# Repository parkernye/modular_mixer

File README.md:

# modular_mixer
Modular Synth 3-channel Mixer

A simple 3-input / 2-output mixer to route sound from the rest of the modular synth to headphones/speaker. 

Future Imporvements:
- Add silkscreen labels to help in assembly
- Source higher quality potentiometers

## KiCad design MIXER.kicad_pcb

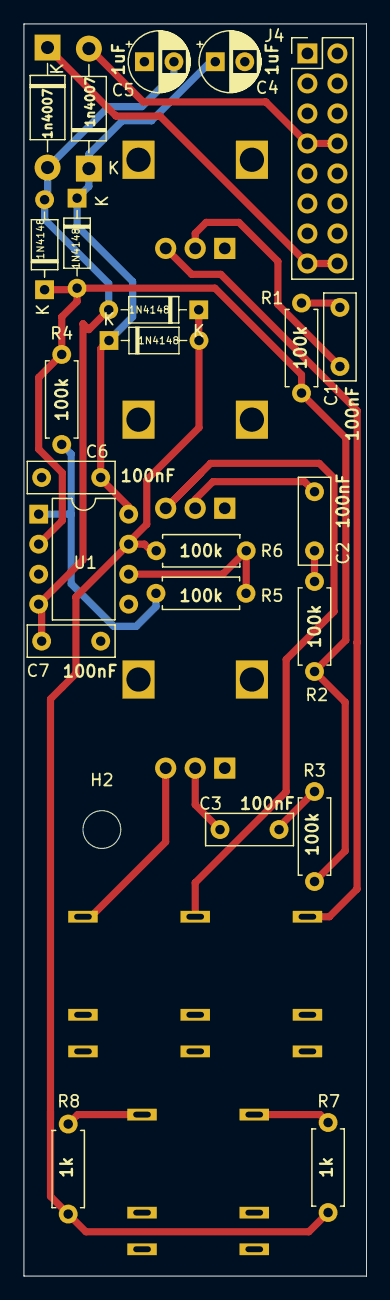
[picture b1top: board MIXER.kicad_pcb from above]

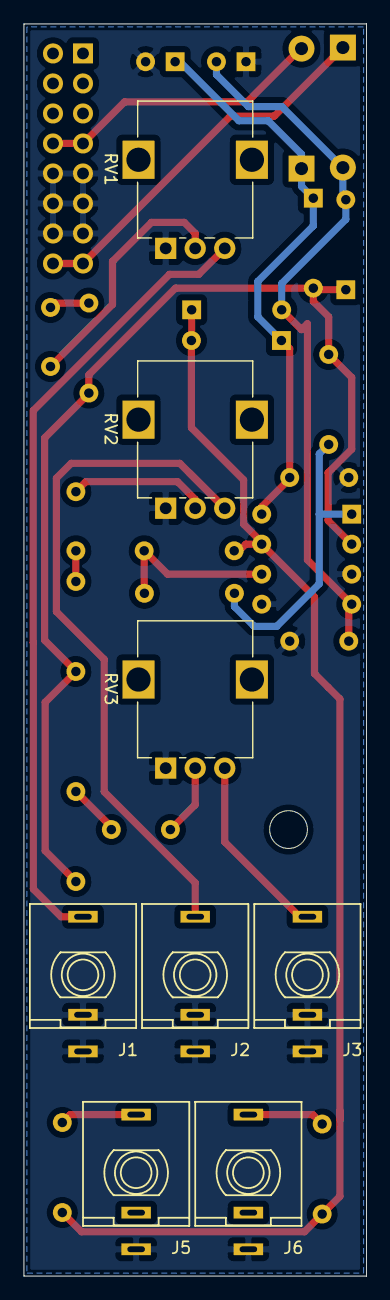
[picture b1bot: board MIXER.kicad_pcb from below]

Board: 2 copper layers, 29.0 x 106.0 mm, 33 parts (8 on the bottom side), 20 nets.

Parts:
C1, C2, C3, C6, C7: 100nF; C_Rect_L7.2mm_W2.5mm_P5.00mm_FKS2_FKP2_MKS2_MKP2
C4, C5: 1uF; CP_Radial_D5.0mm_P2.50mm
D1, D2, D5, D6: 1N4148; D_DO-35_SOD27_P7.62mm_Horizontal
D3, D4: 1N4007; D_DO-41_SOD81_P10.16mm_Horizontal
H1, H2: MountingHole; MountingHole_3.2mm_M3
J1, J2, J3, J5, J6: fuzzySI_thonkiconn; thonkiconn_fuzzySi
J4: Conn_02x08_Odd_Even; PinHeader_2x08_P2.54mm_Vertical
R1, R2, R3, R4, R5, R6: 100K; R_Axial_DIN0207_L6.3mm_D2.5mm_P7.62mm_Horizontal
R7, R8: 1K; R_Axial_DIN0207_L6.3mm_D2.5mm_P7.62mm_Horizontal
RV1, RV2, RV3: 100k; Potentiometer_Alpha_RD901F-40-00D_Single_Vertical
U1: TL072; DIP-8_W7.62mm

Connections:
+12V: C4.1, C6.1, D2.1, D3.1, D5.1, U1.8
-12V: C5.2, C7.2, D1.2, D4.2, D6.2, U1.4
GND: C4.2, C5.1, C6.2, C7.1, J1.1, J1.2, J2.1, J2.2, J3.1, J3.2, J4.9, J4.10, J4.11, J4.12, J4.13, J4.14, J5.1, J6.1, RV1.1, RV2.1, RV3.1, U1.3, U1.5
unnamed: C1.1, RV1.2
unnamed: C1.2, R1.2
unnamed: C2.1, RV2.2
unnamed: C2.2, R2.2
unnamed: C3.1, RV3.2
unnamed: C3.2, R3.2
unnamed: D1.1, D2.2, R1.1, R2.1, R3.1, R4.2, U1.2
unnamed: D5.2, D6.1, R6.1, R7.2, R8.1, U1.7
unnamed: J1.3, RV1.3
unnamed: J2.3, RV2.3
unnamed: J3.3, RV3.3
unnamed: J5.3, R7.1
unnamed: J6.3, R8.2
unnamed: R4.1, R5.2, U1.1
unnamed: R5.1, R6.2, U1.6
VAA: D3.2, J4.7, J4.8
VSS: D4.1, J4.15, J4.16
